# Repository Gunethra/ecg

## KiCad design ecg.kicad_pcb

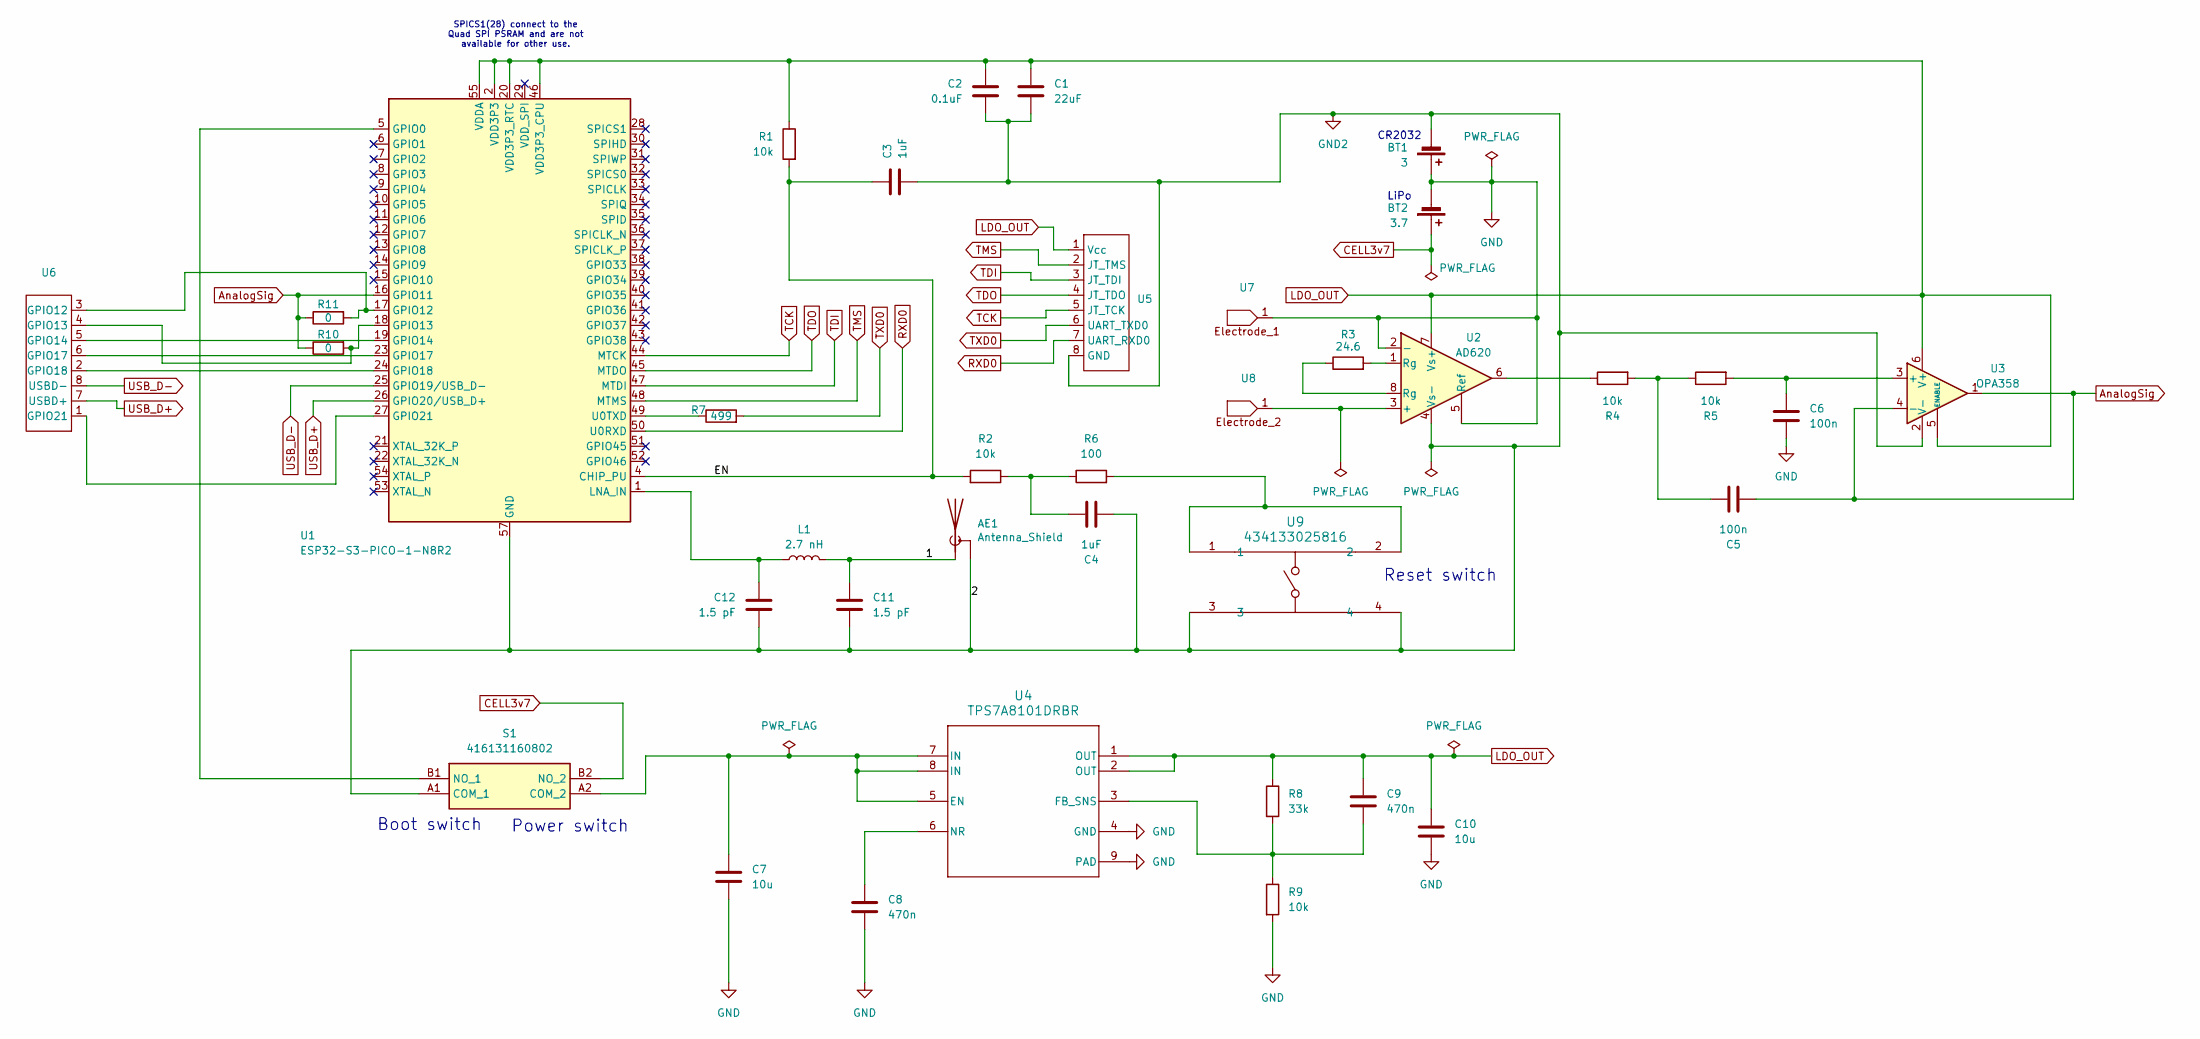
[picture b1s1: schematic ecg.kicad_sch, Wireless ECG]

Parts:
AE1: Antenna_Shield; Texas_SWRA117D_2.4GHz_Right
BT1: 3; TestPoint_Pad_1.0x1.0mm
BT2: 3.7; TestPoint_Pad_1.0x1.0mm
C1: 22uF; C_0603_1608Metric
C2: 0.1uF; C_0603_1608Metric
C3, C4: 1uF; C_0603_1608Metric
C5, C6: 100n; C_0603_1608Metric
C7, C10: 10u; C_0603_1608Metric
C8, C9: 470n; C_0603_1608Metric
C11, C12: 1.5 pF; C_0201_0603Metric
L1: 2.7 nH; L_0201_0603Metric
R1, R2, R4, R5, R9: 10k; R_0603_1608Metric
R3: 24.6; R_0603_1608Metric
R6: 100; R_0603_1608Metric
R7: 499; R_0603_1608Metric
R8: 33k; R_0603_1608Metric
R10, R11: 0; R_0603_1608Metric
S1: 416131160802; Mouser Part Number 710-416131160802
U1: ESP32-S3-PICO-1-N8R2; QFN56_7X7_EXP
U2: AD620; R_8_ADI-M
U3: OPA358; DCK6-M
U4: TPS7A8101DRBR; IC_DRV8601DRBT
U5, U6: Socket_THT_MountingHoles
U7, U8: TestPoint_Pad_1.0x1.0mm
U9: 434133025816; SMD_025816_WRE

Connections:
/1: AE1.1 (A), C11.1, L1.2
/EN: C3.2, R1.2, R2.2, U1.4 (CHIP_PU)
AnalogSig: C5.2, R10.1, R11.1, U1.16 (GPIO11), U3.1, U3.4 (-)
CELL3v7: BT2.1 (+), S1.B2 (NO_2)
GND: BT1.1 (+), BT2.2 (-), C6.2, C7.2, C8.2, C10.2, R9.2, U2.2 (-), U2.5 (Ref), U4.4 (GND), U4.9 (PAD), U7.1
GND2: AE1.2 (Shield), BT1.2 (-), C1.1, C2.1, C3.1, C4.1, C11.2, C12.2, S1.A1 (COM_1), U1.57 (GND), U2.4 (Vs-), U3.2 (V-), U5.8 (GND), U9.3, U9.4
LDO_OUT: C1.2, C2.2, C9.1, C10.1, R1.1, R8.1, U1.2 (VDD3P3), U1.3 (VDD3P3), U1.20 (VDD3P3_RTC), U1.46 (VDD3P3_CPU), U1.55 (VDDA), U1.56 (VDDA), U2.7 (Vs+), U3.5 (ENABLE), U3.6 (V+), U4.1 (OUT), U4.2 (OUT), U5.1 (Vcc)
unnamed: C4.2, R2.1, R6.1
unnamed: C5.1, R4.2, R5.1
unnamed: R3.1, U2.8 (Rg)
unnamed: R3.2, U2.1 (Rg)
unnamed: R4.1, U2.6
unnamed: R6.2, U9.1, U9.2
unnamed: C7.1, S1.A2 (COM_2), U4.5 (EN), U4.7 (IN), U4.8 (IN)
unnamed: S1.B1 (NO_1), U1.5 (GPIO0)
unnamed: R11.2, U1.17 (GPIO12), U6.3 (GPIO12)
unnamed: R10.2, U1.18 (GPIO13), U6.4 (GPIO13)
unnamed: U1.19 (GPIO14), U6.5 (GPIO14)
unnamed: U1.23 (GPIO17), U6.6 (GPIO17)
unnamed: U1.24 (GPIO18), U6.2 (GPIO18)
unnamed: U1.27 (GPIO21), U6.1 (GPIO21)
unnamed: C12.1, L1.1, U1.1 (LNA_IN)
unnamed: R7.1, U1.49 (U0TXD)
unnamed: U2.3 (+), U8.1
unnamed: C6.1, R5.2, U3.3 (+)
unnamed: C9.2, R8.2, R9.1, U4.3 (FB_SNS)
unnamed: C8.1, U4.6 (NR)
RXD0: U1.50 (U0RXD), U5.7 (UART_RXD0)
TCK: U1.44 (MTCK), U5.5 (JT_TCK)
TDI: U1.47 (MTDI), U5.3 (JT_TDI)
TDO: U1.45 (MTDO), U5.4 (JT_TDO)
TMS: U1.48 (MTMS), U5.2 (JT_TMS)
TXD0: R7.2, U5.6 (UART_TXD0)
USB_D+: U1.26 (GPIO20/USB_D+), U6.7 (USBD+)
USB_D-: U1.25 (GPIO19/USB_D-), U6.8 (USBD-)

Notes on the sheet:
Power switch
Reset switch
LiPo
CR2032
Boot switch
SPICS1(28) connect to the Quad SPI PSRAM and are not available for other use.

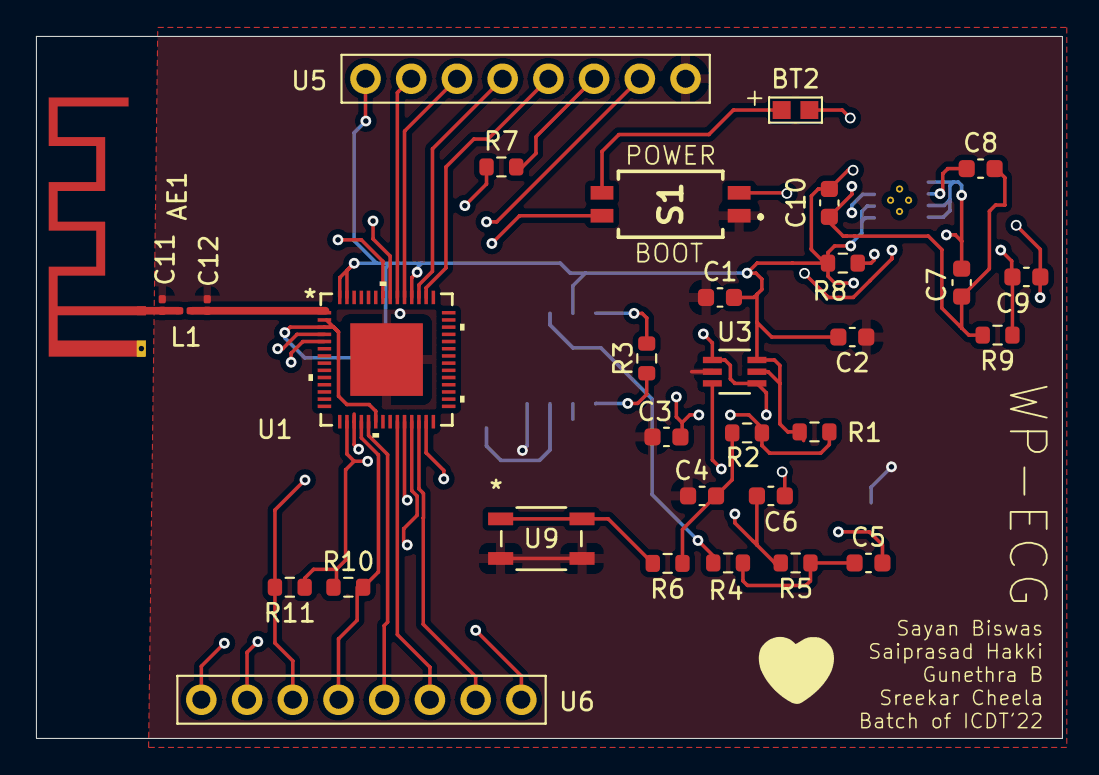
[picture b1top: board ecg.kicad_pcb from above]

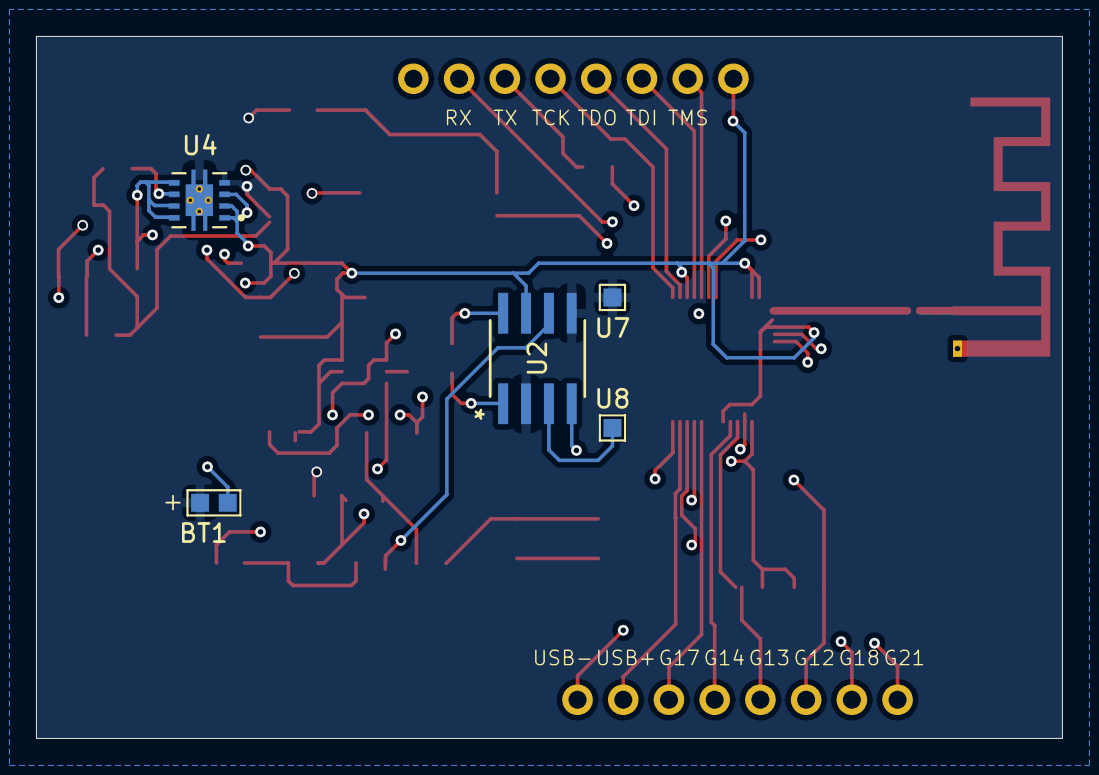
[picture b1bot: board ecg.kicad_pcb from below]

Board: 4 copper layers, 57.0 x 39.0 mm, 37 parts (5 on the bottom side), 35 nets.

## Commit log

2024-03-07 removed high pass
2024-03-07 Modified analog as per sir(Lab)
2024-03-14 Created and added Symbols for previous blackboxes
2024-03-14 Assigned footprints for Resistors and Capacitors
2024-03-14 Move project specific libraries to correct folders
2024-03-14 Connected external oscillator
2024-03-20 Connect unused GPIO pins to Vs-
2024-03-21 Remove external oscillator, connect all GND to VS-, Fix ERC Errors.
2024-03-24 Remove Analog schem sheet
    Remove Analog schem sheet as it has been merged into main sheet(now at A3 sizing.)
2024-03-24 Tinker with Antenna ckt
2024-03-24 Remove XTAL_P, XTAL_N from esp32-s3-pico symbol
2024-04-01 Add 499ohm resistor for UART
2024-04-06 A lot of changes!!!
2024-04-06 LDO, UART, USB
2024-04-06 Added LDO
2024-04-06 Added Footprint for pin sockets and misc. changes
2024-06-02 Up to date with Final PCB sent for fabrication
